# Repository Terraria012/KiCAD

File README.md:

# KiCAD
I recommend not to use these KiCAD data.
Some circuits have problem.

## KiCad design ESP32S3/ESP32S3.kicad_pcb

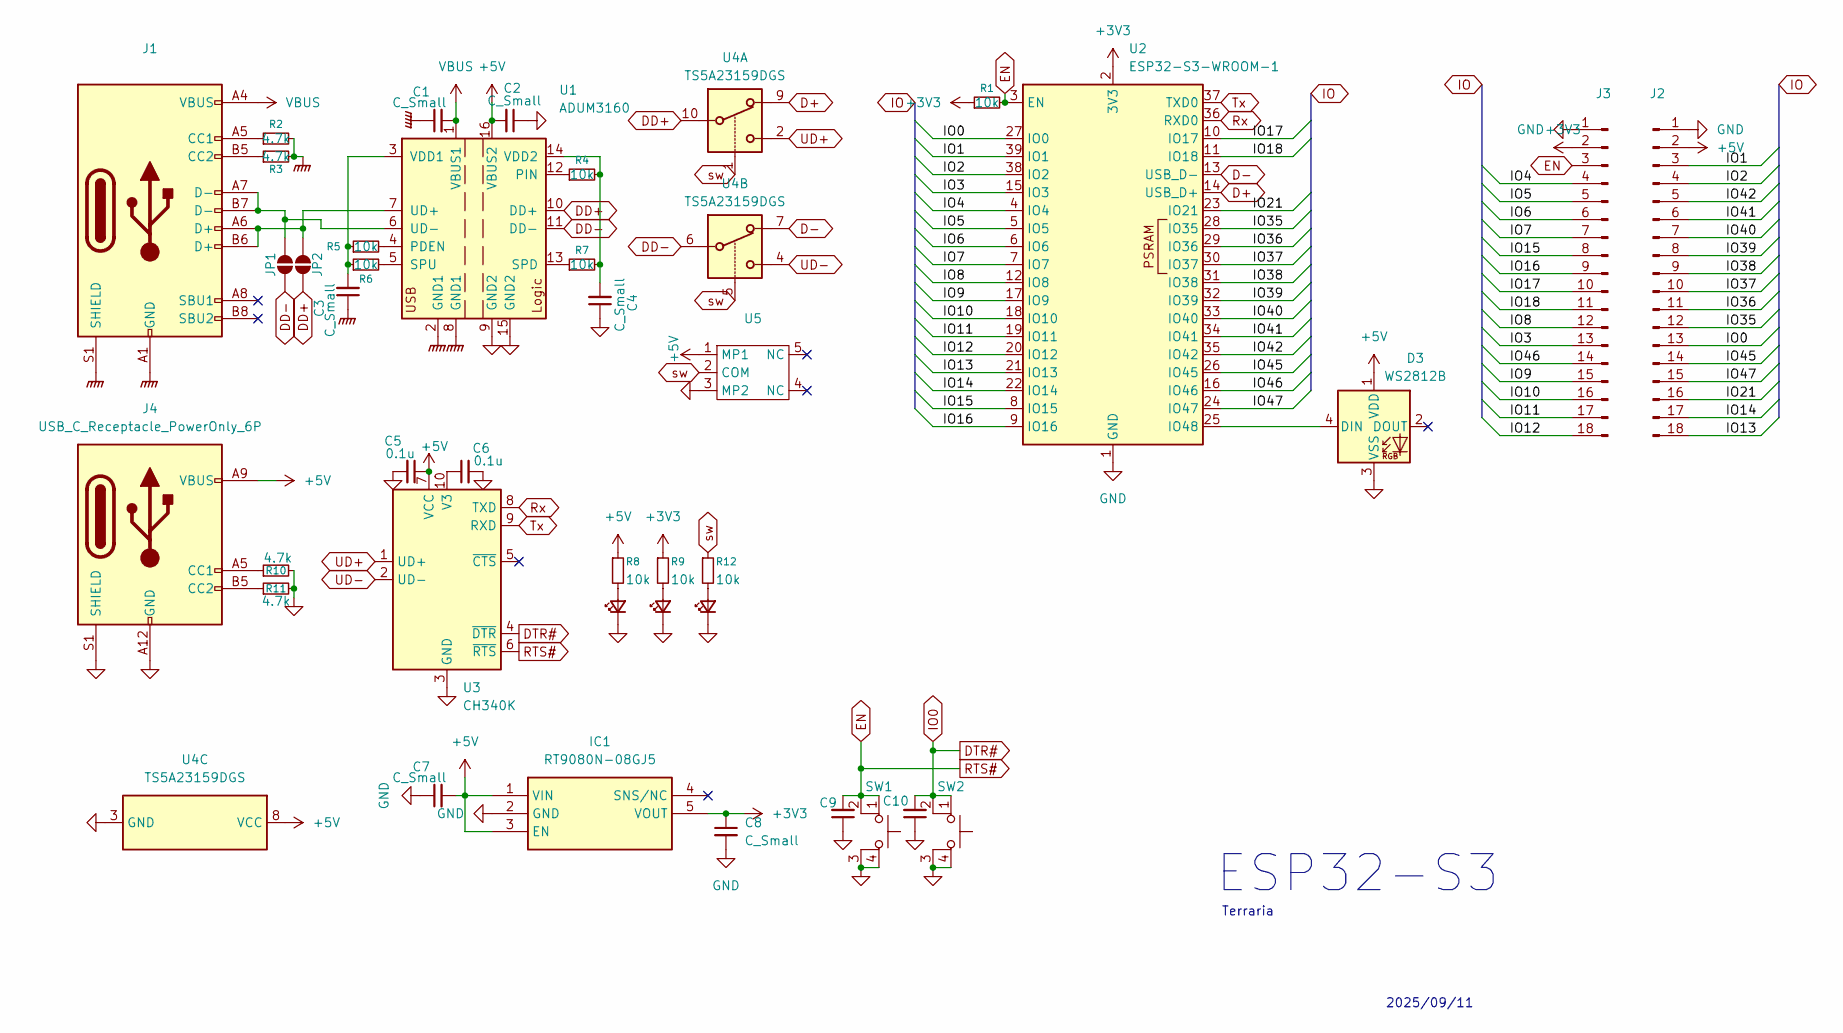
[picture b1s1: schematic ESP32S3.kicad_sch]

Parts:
C1, C2, C3, C4, C7, C8, C9, C10: C_Small; C_0603_1608Metric
C5, C6: 0.1u; C_0603_1608Metric_Pad1.08x0.95mm_HandSolder
D1, D2, D4: LED_Small; LED_0603_1608Metric_Pad1.05x0.95mm_HandSolder
D3: WS2812B; LED_WS2812B_PLCC4_5.0x5.0mm_P3.2mm
IC1: RT9080N-08GJ5; SOT94P280X100-5N; Manufacturer_Part_Number RT9080N-08GJ5; Mouser Part Number 835-RT9080N-08GJ5
J1: USB_C_Receptacle_USB2.0_16P; USB_C_Receptacle_GCT_USB4105-xx-A_16P_TopMnt_Horizontal
J2, J3: Conn_01x18_Pin; PinHeader_1x18_P2.54mm_Vertical
J4: USB_C_Receptacle_PowerOnly_6P; USB_C_Receptacle_GCT_USB4125-xx-x_6P_TopMnt_Horizontal
JP1, JP2: SolderJumper_2_Open; SolderJumper-2_P1.3mm_Open_RoundedPad1.0x1.5mm
R1, R4, R5, R6, R7: 10k; R_0603_1608Metric
R2, R3: 4.7k; R_0603_1608Metric
R8, R9, R12: 10k; R_0603_1608Metric_Pad0.98x0.95mm_HandSolder
R10, R11: 4.7k; R_0603_1608Metric_Pad0.98x0.95mm_HandSolder
SW1, SW2: SW_MEC_5E; SW_SKRPABE010
U1: ADUM3160; SOIC-16W_7.5x10.3mm_P1.27mm
U2: ESP32-S3-WROOM-1
U3: CH340K; SSOP-10-1EP_3.9x4.9mm_P1mm_EP2.1x3.3mm
U4: TS5A23159DGS; VSSOP-10_3x3mm_P0.5mm
U5: SSAJ120100

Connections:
+3V3: C8.1, IC1.5 (VOUT), J3.2, R1.1, R9.1, U2.2 (3V3)
+5V: C2.2, C5.1, C7.2, D3.1 (VDD), IC1.1 (VIN), IC1.3 (EN), J2.2, J4.A9 (VBUS), J4.B9 (VBUS), R8.1, U1.16 (VBUS2), U3.7 (VCC), U4.8 (VCC), U5.1 (MP1)
/IO1: J2.3, U2.39 (IO1)
/IO2: J2.4, U2.38 (IO2)
/IO3: J3.13, U2.15 (IO3)
/IO4: J3.4, U2.4 (IO4)
/IO5: J3.5, U2.5 (IO5)
/IO6: J3.6, U2.6 (IO6)
/IO7: J3.7, U2.7 (IO7)
/IO8: J3.12, U2.12 (IO8)
/IO9: J3.15, U2.17 (IO9)
/IO10: J3.16, U2.18 (IO10)
/IO11: J3.17, U2.19 (IO11)
/IO12: J3.18, U2.20 (IO12)
/IO13: J2.18, U2.21 (IO13)
/IO14: J2.17, U2.22 (IO14)
/IO15: J3.8, U2.8 (IO15)
/IO16: J3.9, U2.9 (IO16)
/IO17: J3.10, U2.10 (IO17)
/IO18: J3.11, U2.11 (IO18)
/IO21: J2.16, U2.23 (IO21)
/IO35: J2.12, U2.28 (IO35)
/IO36: J2.11, U2.29 (IO36)
/IO37: J2.10, U2.30 (IO37)
/IO38: J2.9, U2.31 (IO38)
/IO39: J2.8, U2.32 (IO39)
/IO40: J2.7, U2.33 (IO40)
/IO41: J2.6, U2.34 (IO41)
/IO42: J2.5, U2.35 (IO42)
/IO45: J2.14, U2.26 (IO45)
/IO46: J3.14, U2.16 (IO46)
/IO47: J2.15, U2.24 (IO47)
D+: U2.14 (USB_D+), U4.9
D-: U2.13 (USB_D-), U4.7
DD+: JP2.2 (B), U1.10 (DD+), U4.10
DD-: JP1.2 (B), U1.11 (DD-), U4.6
DTR#: C10.2, J2.13, SW2.1, SW2.2, U2.27 (IO0), U3.4 (~DTR)
EN: C9.2, J3.3, R1.2, SW1.1, SW1.2, U2.3 (EN), U3.6 (~RTS)
GND: C2.1, C4.1, C5.2, C6.2, C7.1, C8.2, C9.1, C10.1, D1.1 (K), D2.1 (K), D3.3 (VSS), D4.1 (K), IC1.2 (GND), J2.1, J3.1, J4.A12 (GND), J4.B12 (GND), J4.S1 (SHIELD), R10.2, R11.2, SW1.3 (K), SW1.4 (A), SW2.3 (K), SW2.4 (A), U1.9 (GND2), U1.15 (GND2), U2.1 (GND), U2.40 (GND), U2.41 (GND), U3.3 (GND), U3.11 (GND), U4.3 (GND), U5.3 (MP2)
GNDPWR: C1.1, C3.1, J1.A1 (GND), J1.A12 (GND), J1.B1 (GND), J1.B12 (GND), J1.S1 (SHIELD), R2.2, R3.2, U1.2 (GND1), U1.8 (GND1)
unnamed: D1.2 (A), R8.2
unnamed: D2.2 (A), R9.2
unnamed: D3.4 (DIN), U2.25 (IO48)
unnamed: D4.2 (A), R12.2
unnamed: J1.A5 (CC1), R2.1
unnamed: J1.B5 (CC2), R3.1
unnamed: J4.A5 (CC1), R10.1
unnamed: J4.B5 (CC2), R11.1
unnamed: J1.A7 (D-), J1.B7 (D-), JP1.1 (A), U1.6 (UD-)
unnamed: J1.A6 (D+), J1.B6 (D+), JP2.1 (A), U1.7 (UD+)
unnamed: R5.2, U1.4 (PDEN)
unnamed: R4.1, U1.12 (PIN)
unnamed: R7.1, U1.13 (SPD)
unnamed: R6.2, U1.5 (SPU)
unnamed: C3.2, R5.1, R6.1, U1.3 (VDD1)
unnamed: C4.2, R4.2, R7.2, U1.14 (VDD2)
unnamed: C6.1, U3.10 (V3)
Rx: U2.36 (RXD0), U3.8 (TXD)
Tx: U2.37 (TXD0), U3.9 (RXD)
UD+: U3.1 (UD+), U4.2
UD-: U3.2 (UD-), U4.4
VBUS: C1.2, J1.A4 (VBUS), J1.A9 (VBUS), J1.B4 (VBUS), J1.B9 (VBUS), U1.1 (VBUS1)
sw: R12.1, U4.1, U4.5, U5.2 (COM)

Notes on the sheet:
ESP32-S3
2025/09/11
Terraria

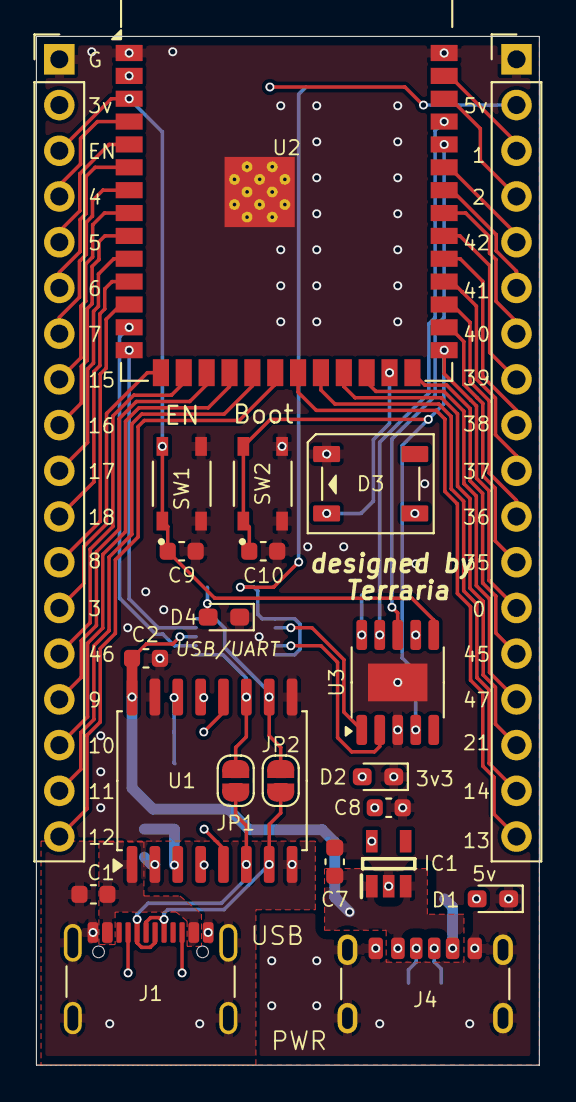
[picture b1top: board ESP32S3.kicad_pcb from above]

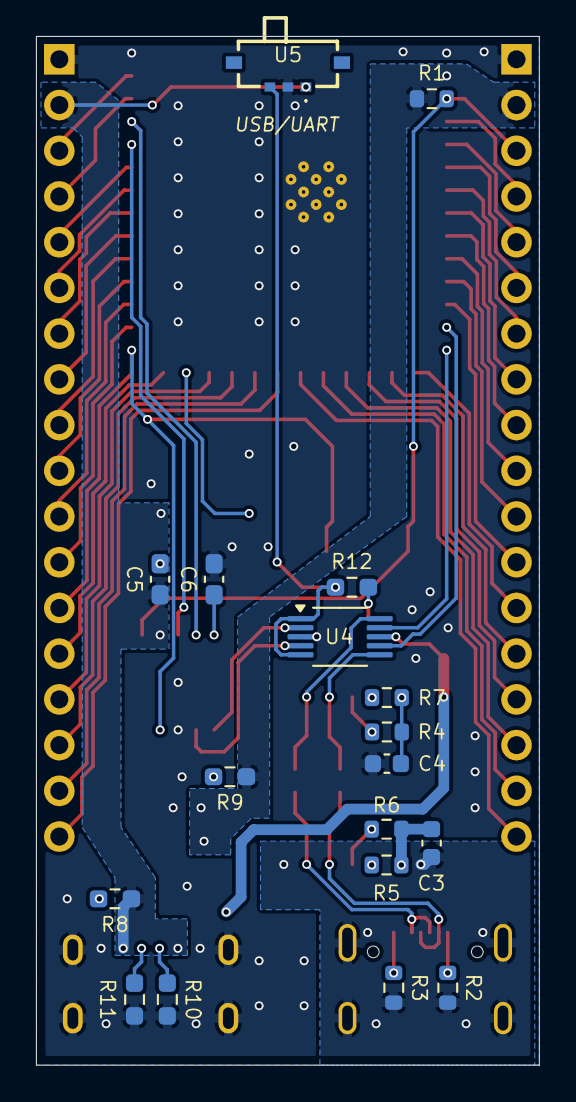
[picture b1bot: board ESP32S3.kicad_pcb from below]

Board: 2 copper layers, 27.9 x 57.1 mm, 40 parts (18 on the bottom side), 63 nets.

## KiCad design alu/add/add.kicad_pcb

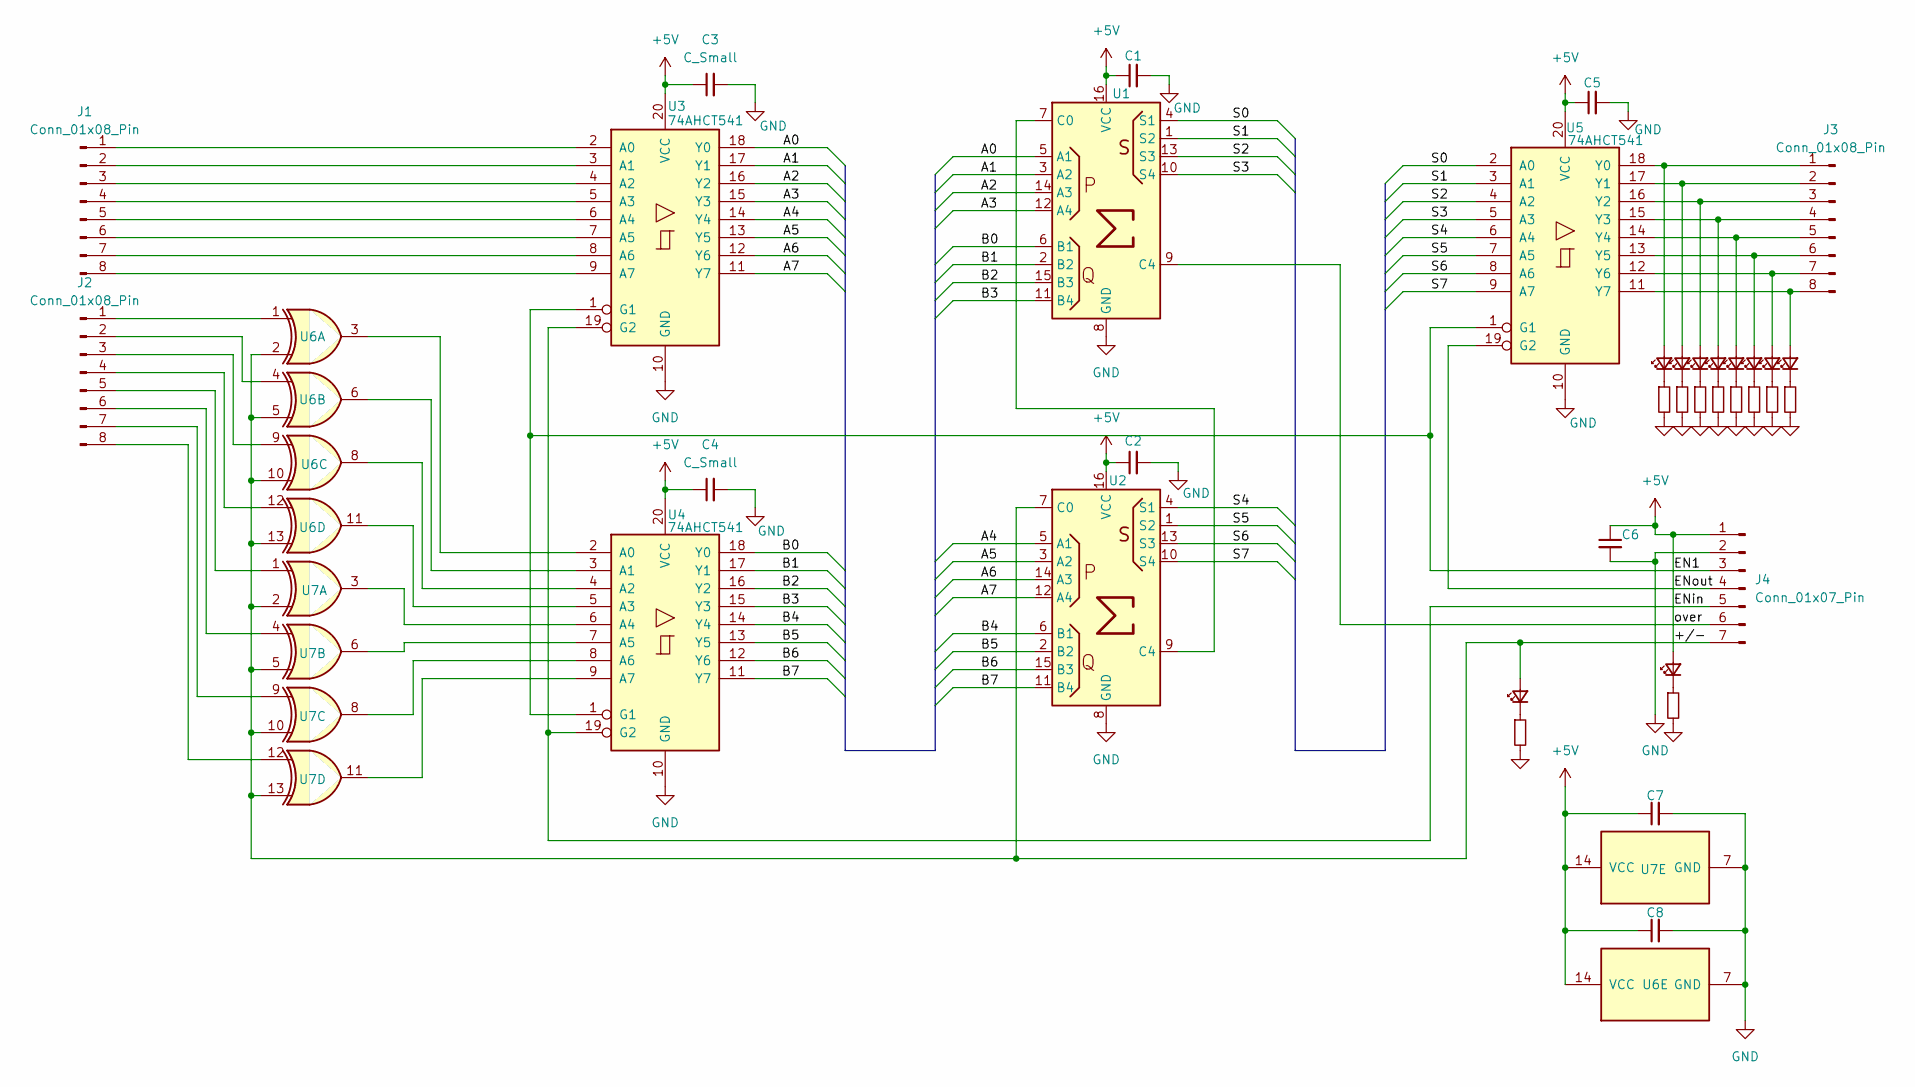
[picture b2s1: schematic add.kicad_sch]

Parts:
C1, C2, C3, C4, C5, C6, C7, C8: C_Small; C_0603_1608Metric_Pad1.08x0.95mm_HandSolder
D1, D2, D3, D4, D5, D6, D7, D8, D9, D10: LED_Small; LED_0603_1608Metric_Pad1.05x0.95mm_HandSolder
J1, J2, J3: Conn_01x08_Pin; PinHeader_1x08_P2.54mm_Vertical
J4: Conn_01x07_Pin; PinHeader_1x07_P2.54mm_Vertical
R1, R2, R3, R4, R5, R6, R7, R8, R9, R10: R_Small; R_0603_1608Metric_Pad0.98x0.95mm_HandSolder
U1, U2: SO-16_3.9x9.9mm_P1.27mm
U3, U4, U5: 74AHCT541; SOIC-20W_7.5x12.8mm_P1.27mm
U6, U7: 74HC86; SOIC-14_3.9x8.7mm_P1.27mm

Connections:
/A0: U1.5 (A1), U3.18 (Y0)
/A1: U1.3 (A2), U3.17 (Y1)
/A2: U1.14 (A3), U3.16 (Y2)
/A3: U1.12 (A4), U3.15 (Y3)
/A4: U2.5 (A1), U3.14 (Y4)
/A5: U2.3 (A2), U3.13 (Y5)
/A6: U2.14 (A3), U3.12 (Y6)
/A7: U2.12 (A4), U3.11 (Y7)
/B0: U1.6 (B1), U4.18 (Y0)
/B1: U1.2 (B2), U4.17 (Y1)
/B2: U1.15 (B3), U4.16 (Y2)
/B3: U1.11 (B4), U4.15 (Y3)
/B4: U2.6 (B1), U4.14 (Y4)
/B5: U2.2 (B2), U4.13 (Y5)
/B6: U2.15 (B3), U4.12 (Y6)
/B7: U2.11 (B4), U4.11 (Y7)
/S0: U1.4 (S1), U5.2 (A0)
/S1: U1.1 (S2), U5.3 (A1)
/S2: U1.13 (S3), U5.4 (A2)
/S3: U1.10 (S4), U5.5 (A3)
/S4: U2.4 (S1), U5.6 (A4)
/S5: U2.1 (S2), U5.7 (A5)
/S6: U2.13 (S3), U5.8 (A6)
/S7: U2.10 (S4), U5.9 (A7)
GND: C1.2, C2.2, C3.2, C4.2, C5.2, C6.2, C7.2, C8.2, J4.2, R1.2, R2.2, R3.2, R4.2, R5.2, R6.2, R7.2, R8.2, R9.2, R10.2, U1.8 (GND), U2.8 (GND), U3.10 (GND), U4.10 (GND), U5.10 (GND), U6.7 (GND), U7.7 (GND)
unnamed: D1.2 (A), J3.1, U5.18 (Y0)
unnamed: D1.1 (K), R1.1
unnamed: D2.2 (A), J3.2, U5.17 (Y1)
unnamed: D2.1 (K), R2.1
unnamed: D3.2 (A), J3.3, U5.16 (Y2)
unnamed: D3.1 (K), R3.1
unnamed: D4.2 (A), J3.4, U5.15 (Y3)
unnamed: D4.1 (K), R4.1
unnamed: D5.2 (A), J3.5, U5.14 (Y4)
unnamed: D5.1 (K), R5.1
unnamed: D6.2 (A), J3.6, U5.13 (Y5)
unnamed: D6.1 (K), R6.1
unnamed: D7.2 (A), J3.7, U5.12 (Y6)
unnamed: D7.1 (K), R7.1
unnamed: D8.2 (A), J3.8, U5.11 (Y7)
unnamed: D8.1 (K), R8.1
unnamed: D9.1 (K), R9.1
unnamed: D10.1 (K), R10.1
unnamed: J1.1, U3.2 (A0)
unnamed: J1.2, U3.3 (A1)
unnamed: J1.3, U3.4 (A2)
unnamed: J1.4, U3.5 (A3)
unnamed: J1.5, U3.6 (A4)
unnamed: J1.6, U3.7 (A5)
unnamed: J1.7, U3.8 (A6)
unnamed: J1.8, U3.9 (A7)
unnamed: J2.1, U6.1
unnamed: J2.2, U6.4
unnamed: J2.3, U6.9
unnamed: J2.4, U6.12
unnamed: J2.5, U7.1
unnamed: J2.6, U7.4
unnamed: J2.7, U7.9
unnamed: J2.8, U7.12
unnamed: U1.7 (C0), U2.9 (C4)
unnamed: U4.2 (A0), U6.3
unnamed: U4.3 (A1), U6.6
unnamed: U4.4 (A2), U6.8
unnamed: U4.5 (A3), U6.11
unnamed: U4.6 (A4), U7.3
unnamed: U4.7 (A5), U7.6
unnamed: U4.8 (A6), U7.8
unnamed: U4.9 (A7), U7.11

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
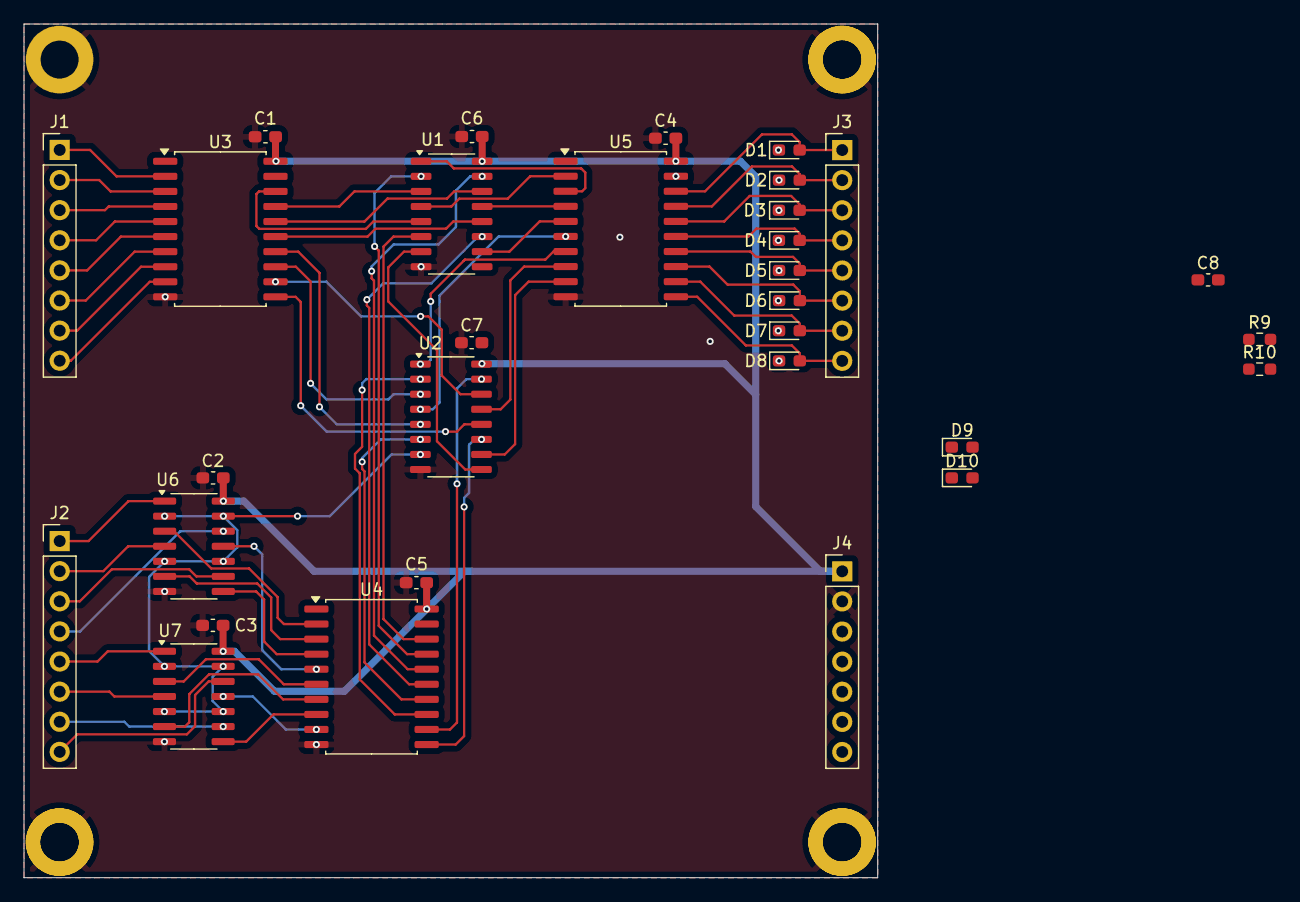
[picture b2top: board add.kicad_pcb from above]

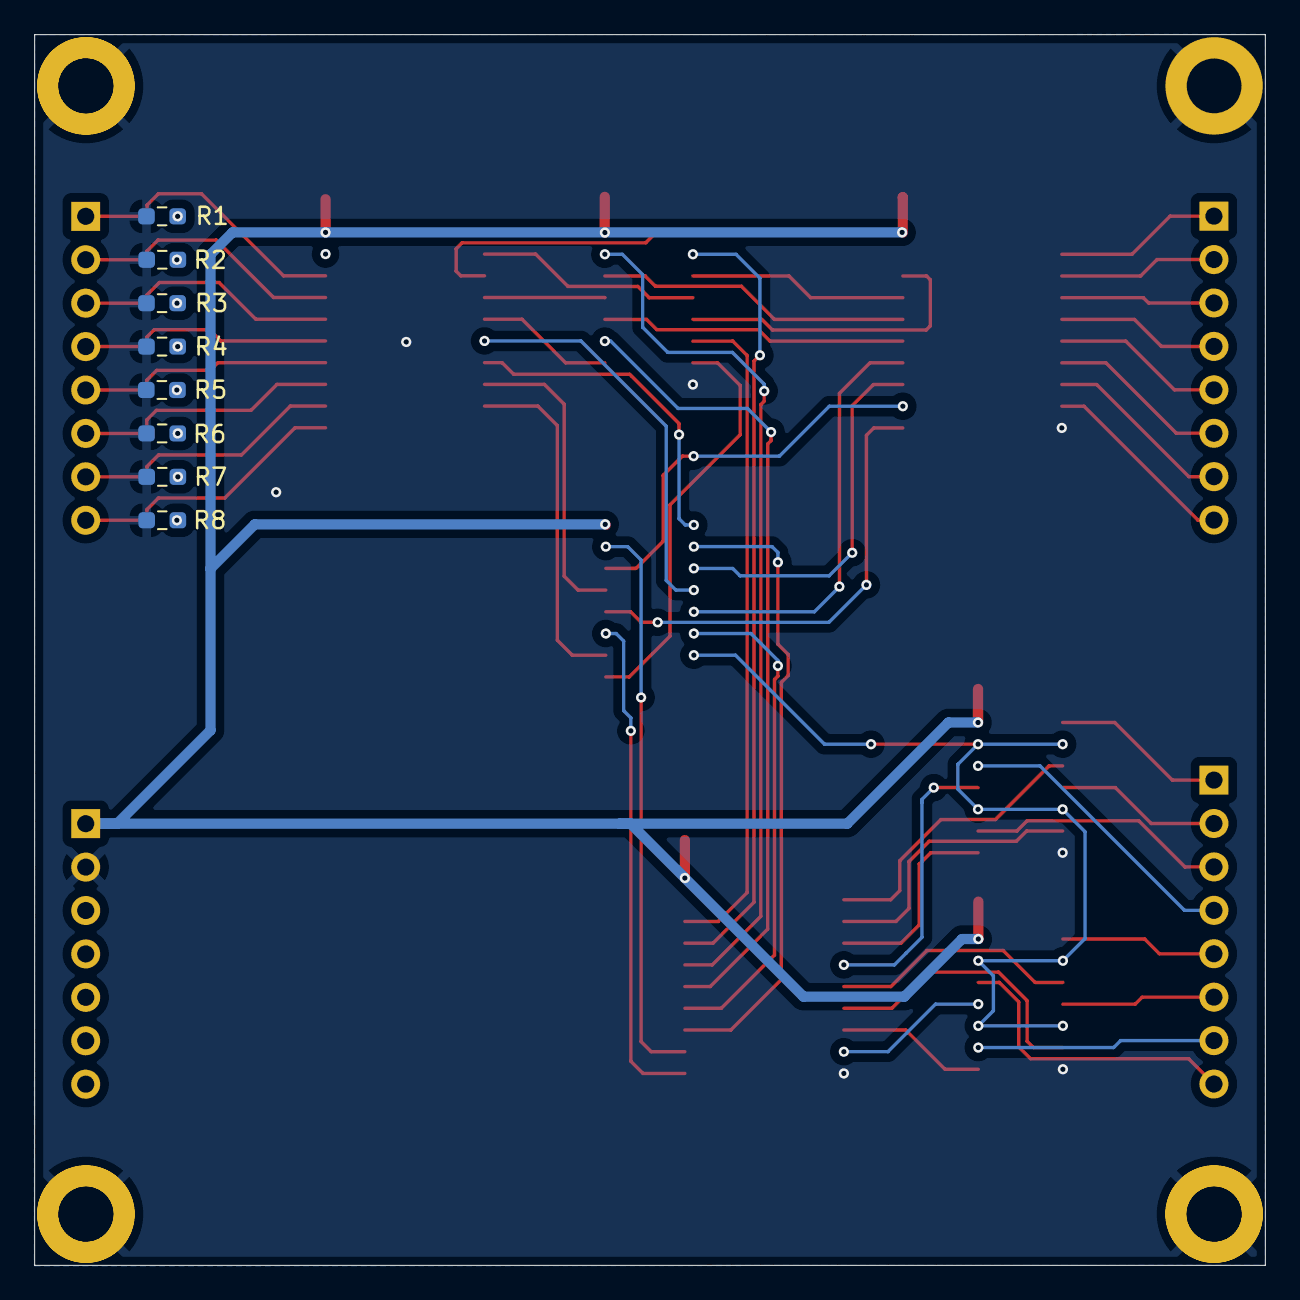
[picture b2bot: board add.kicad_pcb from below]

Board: 2 copper layers, 72.0 x 72.0 mm, 39 parts (8 on the bottom side), 74 nets.

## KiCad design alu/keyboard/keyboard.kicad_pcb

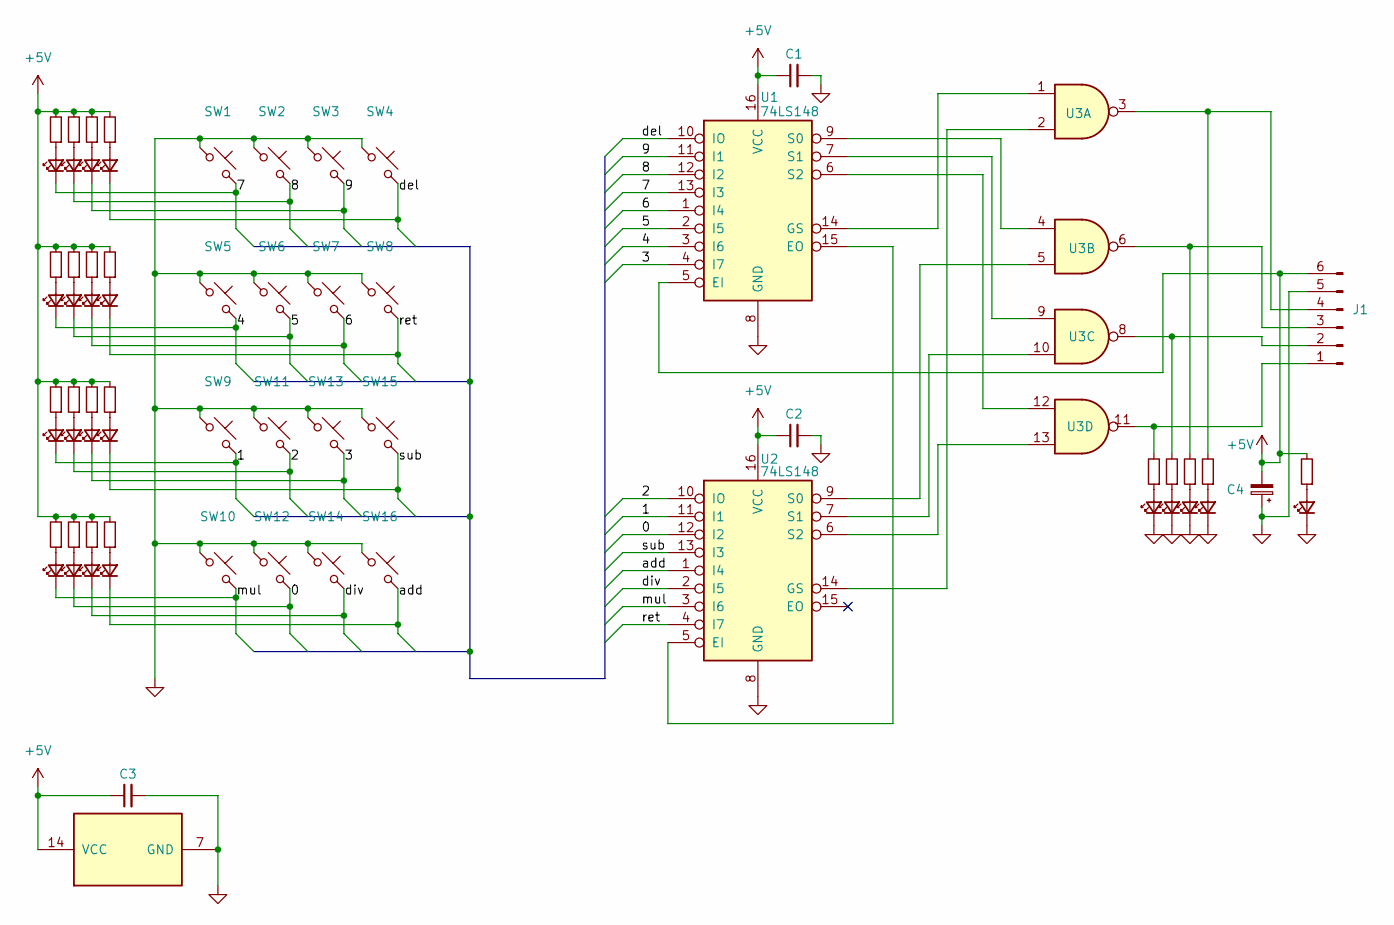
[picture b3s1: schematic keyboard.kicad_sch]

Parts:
C1, C2, C3: C_Small; C_0603_1608Metric
C4: C_Polarized_Small; CP_Radial_D8.0mm_P3.50mm
D1, D2, D3, D4, D5, D6, D7, D8, D9, D10, D11, D12, D13, D14, D15, D16, D17, D18, D19, D20: LED_Small; LED_0603_1608Metric
D21: LED_Small; LED_Rectangular_W3.0mm_H2.0mm
J1: Conn_01x06_Pin; PinHeader_1x06_P2.54mm_Vertical
R1, R2, R3, R4, R5, R6, R7, R8, R9, R10, R11, R12, R13, R14, R15, R16, R17, R18, R19, R20, R21: R_Small; R_0603_1608Metric
SW1, SW2, SW3, SW4, SW5, SW6, SW7, SW8, SW9, SW10, SW11, SW12, SW13, SW14, SW15, SW16: SW_Push_45deg; chocswbrown
U1, U2: 74LS148; DIP-16_W7.62mm
U3: 74HC00; DIP-14_W7.62mm_SMDSocket_SmallPads

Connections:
+5V: C1.1, C2.1, C3.1, C4.2, J1.6, R1.2, R2.2, R3.2, R4.2, R5.2, R6.2, R7.2, R8.2, R9.2, R10.2, R11.2, R12.2, R13.2, R14.2, R15.2, R16.2, R21.2, U1.5 (EI), U1.16 (VCC), U2.16 (VCC), U3.14 (VCC)
/0: D2.1 (K), SW12.2, U2.12 (I2)
/1: D8.1 (K), SW9.2, U2.11 (I1)
/2: D7.1 (K), SW11.2, U2.10 (IO)
/3: D6.1 (K), SW13.2, U1.4 (I7)
/4: D16.1 (K), SW5.2, U1.3 (I6)
/5: D14.1 (K), SW6.2, U1.2 (I5)
/6: D12.1 (K), SW7.2, U1.1 (I4)
/7: D15.1 (K), SW1.2, U1.13 (I3)
/8: D13.1 (K), SW2.2, U1.12 (I2)
/9: D11.1 (K), SW3.2, U1.11 (I1)
/add: D4.1 (K), SW16.2, U2.1 (I4)
/del: D9.1 (K), SW4.2, U1.10 (IO)
/div: D3.1 (K), SW14.2, U2.2 (I5)
/mul: D1.1 (K), SW10.2, U2.3 (I6)
/ret: D10.1 (K), SW8.2, U2.4 (I7)
/sub: D5.1 (K), SW15.2, U2.13 (I3)
GND: C1.2, C2.2, C3.2, C4.1, D17.1 (K), D18.1 (K), D19.1 (K), D20.1 (K), D21.1 (K), J1.5, SW1.1, SW2.1, SW3.1, SW4.1, SW5.1, SW6.1, SW7.1, SW8.1, SW9.1, SW10.1, SW11.1, SW12.1, SW13.1, SW14.1, SW15.1, SW16.1, U1.8 (GND), U2.8 (GND), U3.7 (GND)
unnamed: D1.2 (A), R4.1
unnamed: D2.2 (A), R3.1
unnamed: D3.2 (A), R2.1
unnamed: D4.2 (A), R1.1
unnamed: D5.2 (A), R5.1
unnamed: D6.2 (A), R6.1
unnamed: D7.2 (A), R7.1
unnamed: D8.2 (A), R8.1
unnamed: D9.2 (A), R9.1
unnamed: D10.2 (A), R10.1
unnamed: D11.2 (A), R11.1
unnamed: D12.2 (A), R12.1
unnamed: D13.2 (A), R13.1
unnamed: D14.2 (A), R14.1
unnamed: D15.2 (A), R15.1
unnamed: D16.2 (A), R16.1
unnamed: D17.2 (A), R17.1
unnamed: D18.2 (A), R18.1
unnamed: D19.2 (A), R19.1
unnamed: D20.2 (A), R20.1
unnamed: D21.2 (A), R21.1
unnamed: J1.1, R17.2, U3.11
unnamed: J1.2, R18.2, U3.8
unnamed: J1.3, R19.2, U3.6
unnamed: J1.4, R20.2, U3.3
unnamed: U1.15 (EO), U2.5 (EI)
unnamed: U1.14 (GS), U3.1
unnamed: U1.9 (S0), U3.4
unnamed: U1.7 (S1), U3.9
unnamed: U1.6 (S2), U3.12
unnamed: U2.14 (GS), U3.2
unnamed: U2.9 (S0), U3.5
unnamed: U2.7 (S1), U3.10
unnamed: U2.6 (S2), U3.13

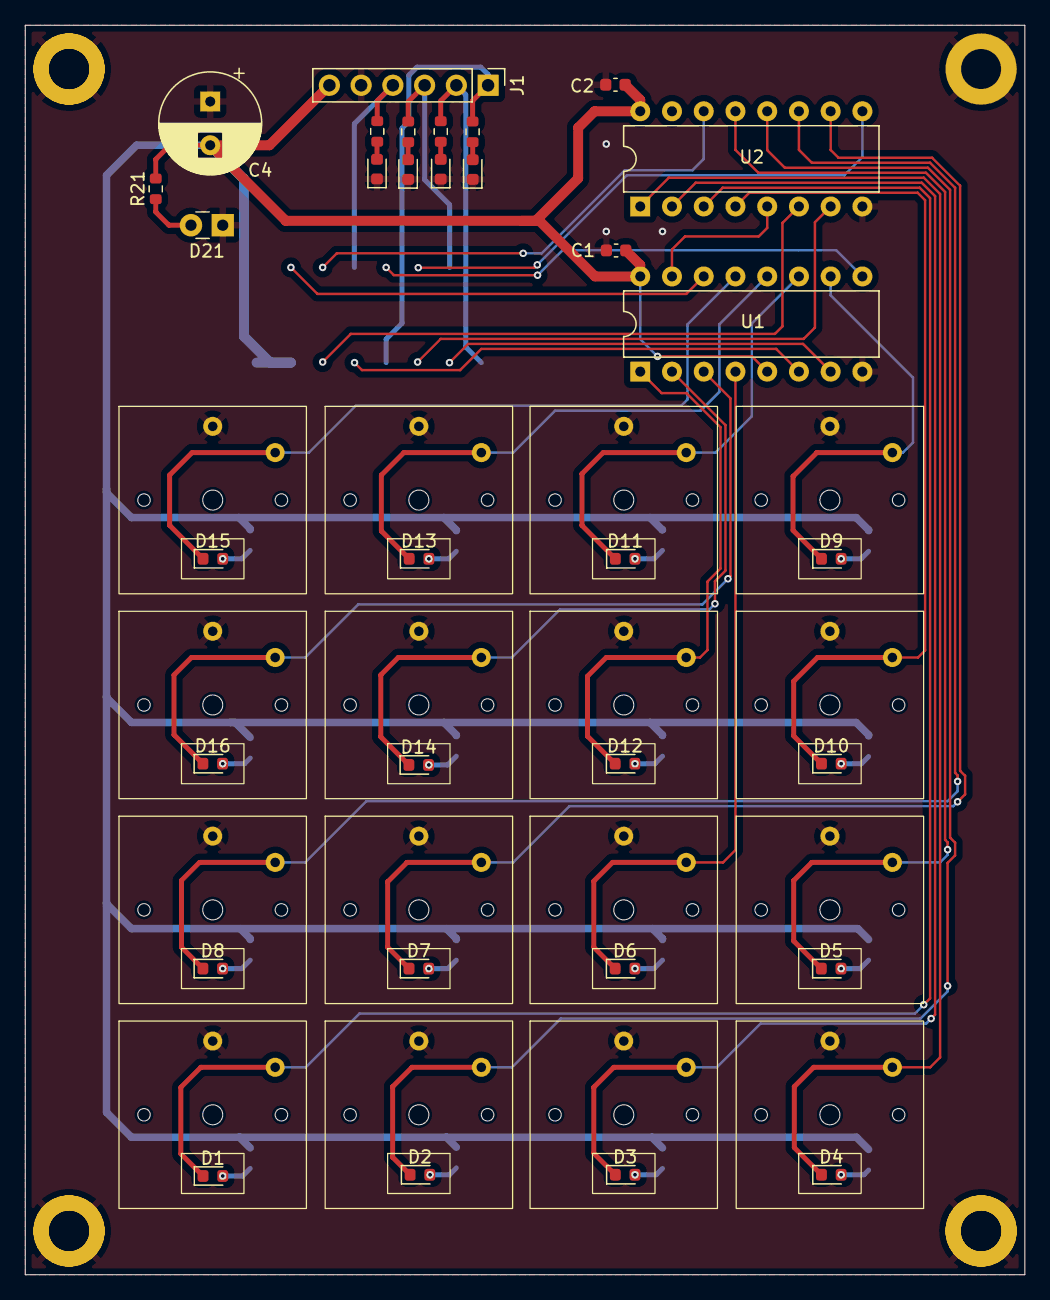
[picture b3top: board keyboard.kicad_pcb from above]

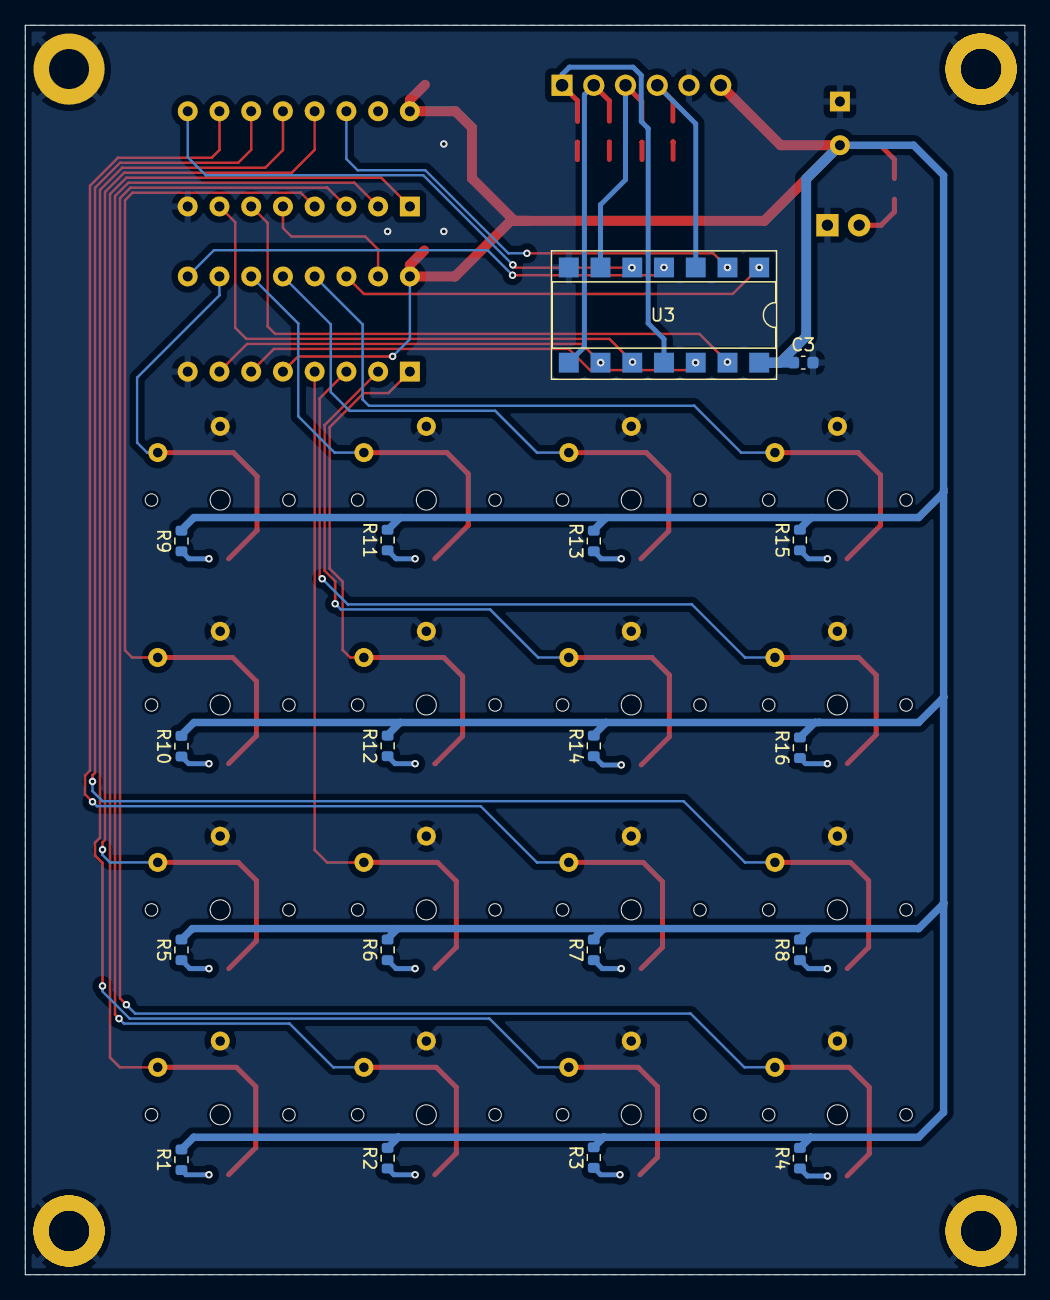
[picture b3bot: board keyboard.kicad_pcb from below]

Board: 2 copper layers, 80.0 x 100.0 mm, 66 parts (18 on the bottom side), 52 nets.
